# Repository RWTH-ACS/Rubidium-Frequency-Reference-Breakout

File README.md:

# Low-Cost Rubidium-Based Clock Reference

This project contains a hardware breakout board for an FE-5680A frequency reference, including a Python web UI to control the frequency offsets and monitor the PPS and Lock signal.

A detailed explanation is given in the publication proceedings of ISPCS 2026 (Low-Cost Rubidium-Based Clock Reference and Pulse-Per-Second Jitter Evaluation)

## Hardware

The hardware breakout board provides multiple decoupled 10 MHz outputs to allow for easy use in a laboratory environment. It also has a pulse per second output that is controllable in its pulse width.

## Software

The software stack allows for a simple control of the RFS via a Raspberry Pi. A USB to RS232 adapter that is connected to the RFS was utilized.

## License

This software is licensed under the Apache open-source license, while the hardware is under the CERN-OHL-W-2.0 open source license. Please refer to the license file in the `LICENSE` in the hardware and software directory.

We kindly ask all academic publications employing components of this work to cite the following paper:

For other licensing options please consult [Prof. Antonello Monti](mailto:amonti@eonerc.rwth-aachen.de).

## Contact

- Manuel Pitz <manuel.pitz@eonerc.rwth-aachen.de>
- Sebastian Uerlich <sebastian.uerlich@eonerc.rwth-aachen.de>
- Benish Khan <benish.khan@eonerc.rwth-aachen.de>
- Leonid Kalinin <leonid.kalinin@rwth-aachen.de>

[Institute for Automation of Complex Power Systems (ACS)](http://www.acs.eonerc.rwth-aachen.de)
[EON Energy Research Center (EONERC)](http://www.eonerc.rwth-aachen.de)
[RWTH University Aachen, Germany](http://www.rwth-aachen.de)

## Acknowledgment

This research has received funding from the European Union’s Horizon Europe research and innovation programme under grant agreement No 101172829. Views and opinions expressed are however those of the author(s) only and do not necessarily reflect those of the European Union or CINEA. Neither the European Union nor the granting authority can be held responsible for them.

We are grateful for the financial support of the [BMWE (Federal Ministry of Economic Affairs and Energy)](https://www.bundeswirtschaftsministerium.de/Navigation/EN/Home/home.html), funding reference [03EI6125A](https://www.enargus.de/pub/bscw.cgi/?op=enargus.eps2&q=beaver&v=10&id=243841191).

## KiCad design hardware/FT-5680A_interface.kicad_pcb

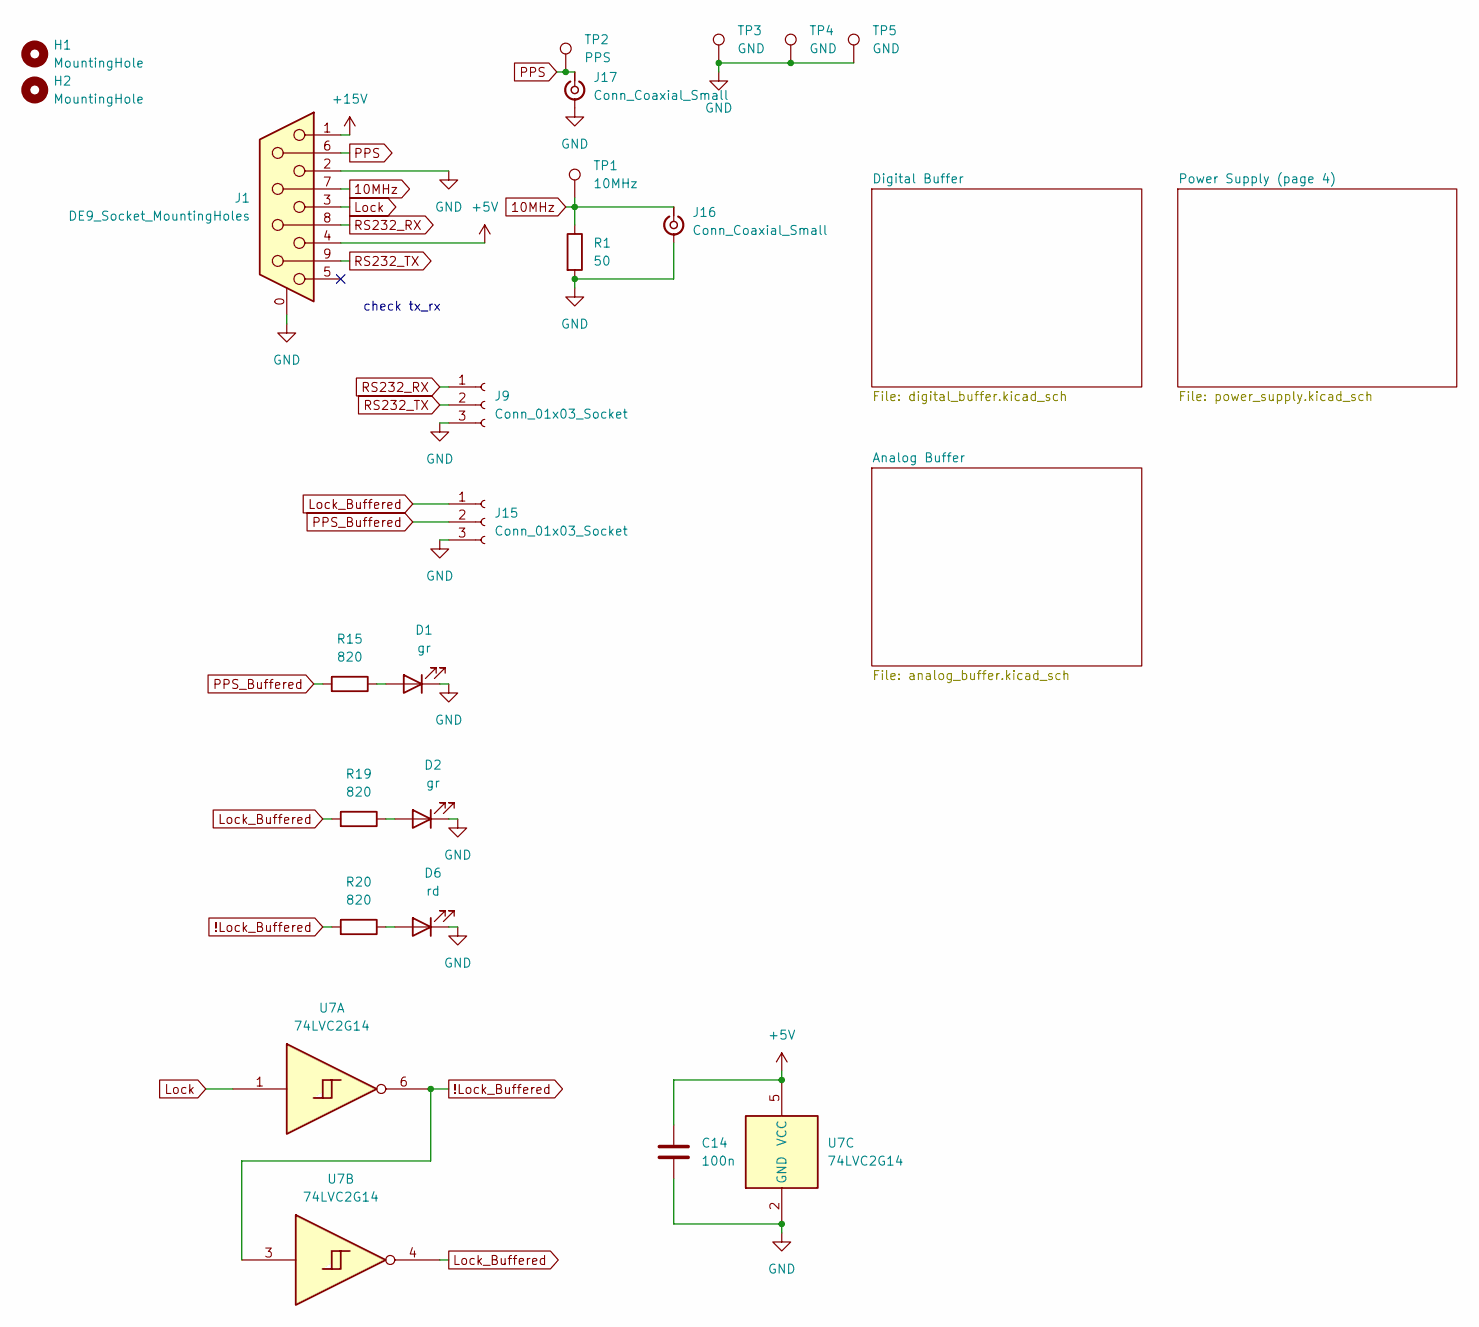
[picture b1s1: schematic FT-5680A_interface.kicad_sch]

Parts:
C14: 100n; C_0805_2012Metric_Pad1.18x1.45mm_HandSolder
D1, D2: gr; LED_0805_2012Metric_Pad1.15x1.40mm_HandSolder
D6: rd; LED_0805_2012Metric_Pad1.15x1.40mm_HandSolder
H1, H2: MountingHole; MountingHole_4.3mm_M4_DIN965
J1: DE9_Socket_MountingHoles; ASSMANN_A-DF_09_A_KG-T2S; Digikey AE10921-ND
J9, J15: Conn_01x03_Socket; 2601-3103; Digikey 2946-2601-3103-ND
J16, J17: Conn_Coaxial_Small; SMA_Molex_73251-1153_EdgeMount_Horizontal
R1: 50; R_0805_2012Metric_Pad1.20x1.40mm_HandSolder
R15, R19, R20: 820; R_0805_2012Metric_Pad1.20x1.40mm_HandSolder
TP1: 10MHz; PinHeader_1x01_P1.00mm_Vertical
TP2: PPS; PinHeader_1x01_P1.00mm_Vertical
TP3, TP4, TP5: GND; PinHeader_1x01_P1.00mm_Vertical
U7: 74LVC2G14; SOT-363_SC-70-6_Handsoldering; Digikey 296-13011-1-ND

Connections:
10MHz: J1.7, J16.1 (In), R1.1, TP1.1; also elsewhere on the board
!Lock_Buffered: R20.2, U7.3, U7.6
+5V: C14.1, J1.4, U7.5 (VCC); also elsewhere on the board
+15V: J1.1; also elsewhere on the board
GND: C14.2, D1.1 (K), D2.1 (K), D6.1 (K), J1.0 (PAD), J1.2, J9.3, J15.3, J16.2 (Ext), J17.2 (Ext), R1.2, TP3.1, TP4.1, TP5.1, U7.2 (GND); also elsewhere on the board
Lock: J1.3, U7.1
Lock_Buffered: J15.1, R19.2, U7.4
unnamed: D1.2 (A), R15.1
unnamed: D2.2 (A), R19.1
unnamed: D6.2 (A), R20.1
PPS: J1.6, J17.1 (In), TP2.1; also elsewhere on the board
PPS_Buffered: J15.2, R15.2; also elsewhere on the board
RS232_RX: J1.8, J9.1
RS232_TX: J1.9, J9.2

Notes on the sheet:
check tx_rx

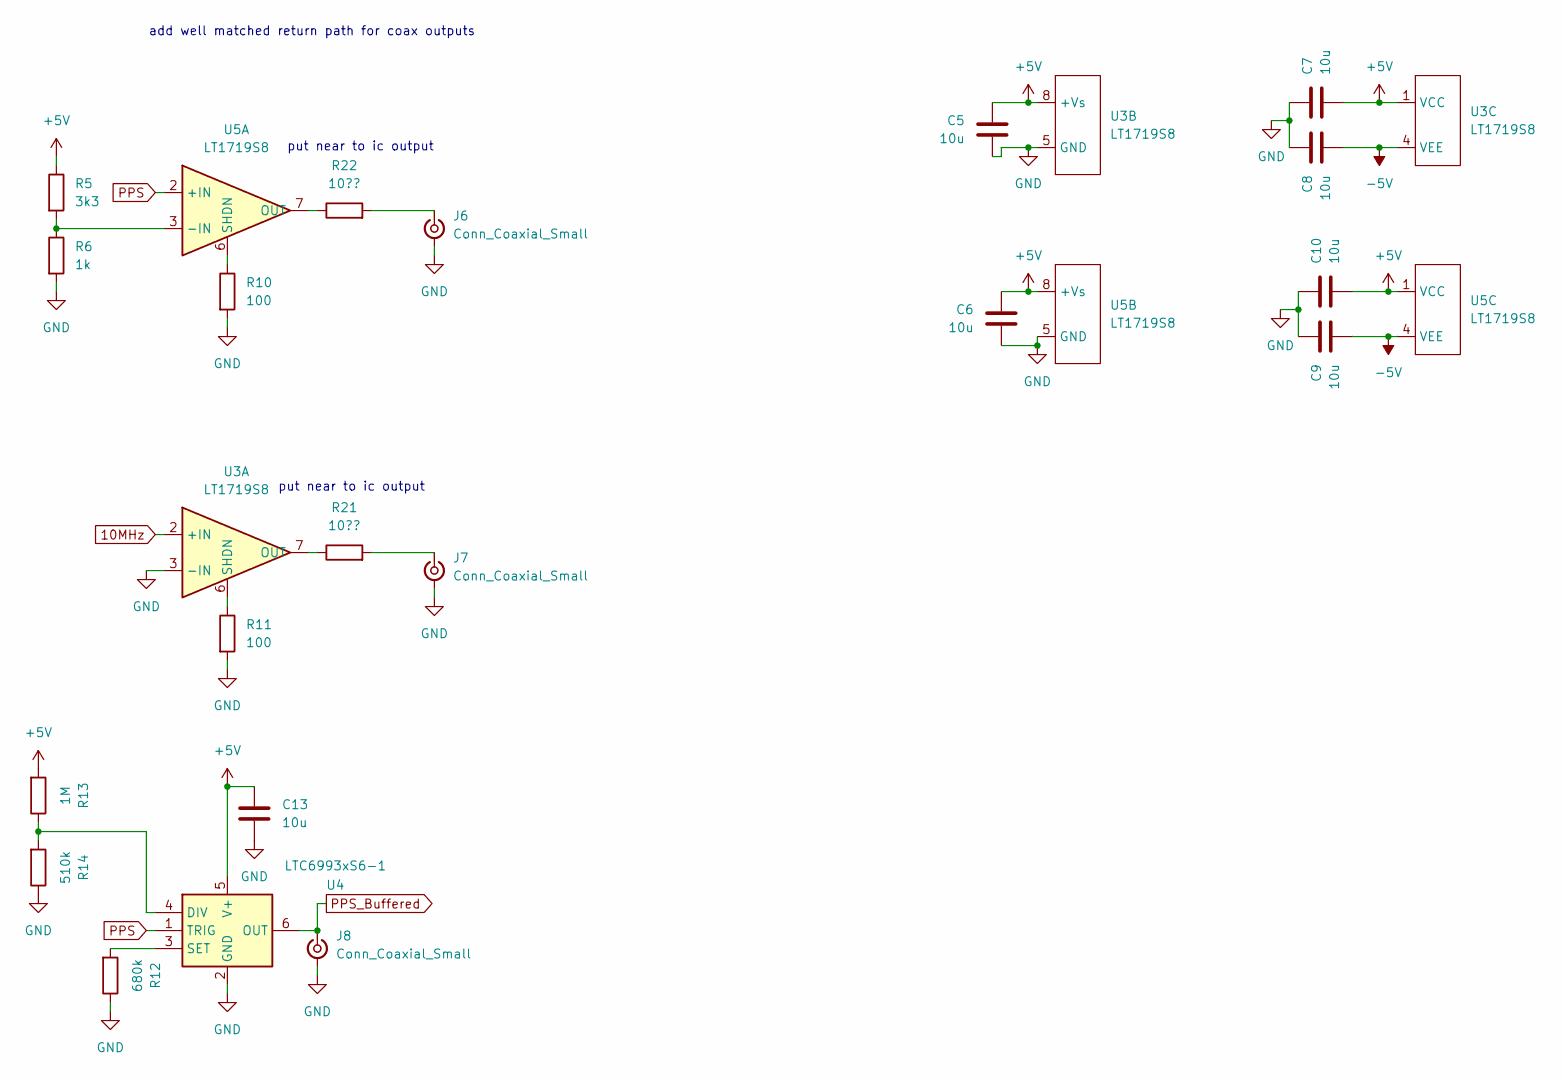
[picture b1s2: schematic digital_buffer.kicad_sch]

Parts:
C5, C6, C7, C8, C9, C10, C13: 10u; C_0805_2012Metric_Pad1.18x1.45mm_HandSolder
J6, J7, J8: Conn_Coaxial_Small; SMA_Molex_73251-1153_EdgeMount_Horizontal
R5: 3k3; R_0805_2012Metric_Pad1.20x1.40mm_HandSolder
R6: 1k; R_0805_2012Metric_Pad1.20x1.40mm_HandSolder
R10, R11: 100; R_0805_2012Metric_Pad1.20x1.40mm_HandSolder
R12: 680k; R_0805_2012Metric_Pad1.20x1.40mm_HandSolder
R13: 1M; R_0805_2012Metric_Pad1.20x1.40mm_HandSolder
R14: 510k; R_0805_2012Metric_Pad1.20x1.40mm_HandSolder
R21, R22: 10??; R_0805_2012Metric_Pad1.20x1.40mm_HandSolder
U3, U5: LT1719S8; SOIC-8_3.9x4.9mm_P1.27mm; Digikey 505-LT1719IS8#PBF-ND
U4: LTC6993xS6-1; TSOT-23-6_HandSoldering; Digikey 505-LTC6993HS6-1#WTRMPBFCT-ND

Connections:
10MHz: U3.2 (+IN); also elsewhere on the board
+5V: C5.1, C6.1, C7.2, C10.2, C13.1, R5.1, R13.2, U3.1 (VCC), U3.8 (+Vs), U4.5 (V+), U5.1 (VCC), U5.8 (+Vs); also elsewhere on the board
-5V: C8.2, C9.2, U3.4 (VEE), U5.4 (VEE); also elsewhere on the board
GND: C5.2, C6.2, C7.1, C8.1, C9.1, C10.1, C13.2, J6.2 (Ext), J7.2 (Ext), J8.2 (Ext), R6.2, R10.2, R11.2, R12.1, R14.1, U3.3 (-IN), U3.5 (GND), U4.2 (GND), U5.5 (GND); also elsewhere on the board
unnamed: J6.1 (In), R22.1, R22.2, U5.7 (OUT)
unnamed: J7.1 (In), R21.1, R21.2, U3.7 (OUT)
unnamed: R11.1, U3.6 (SHDN)
unnamed: R13.1, R14.2, U4.4 (DIV)
unnamed: R12.2, U4.3 (SET)
unnamed: R5.2, R6.1, U5.3 (-IN)
unnamed: R10.1, U5.6 (SHDN)
PPS: U4.1 (TRIG), U5.2 (+IN); also elsewhere on the board
PPS_Buffered: J8.1 (In), U4.6 (OUT); also elsewhere on the board

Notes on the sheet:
put near to ic output
add well matched return path for coax outputs

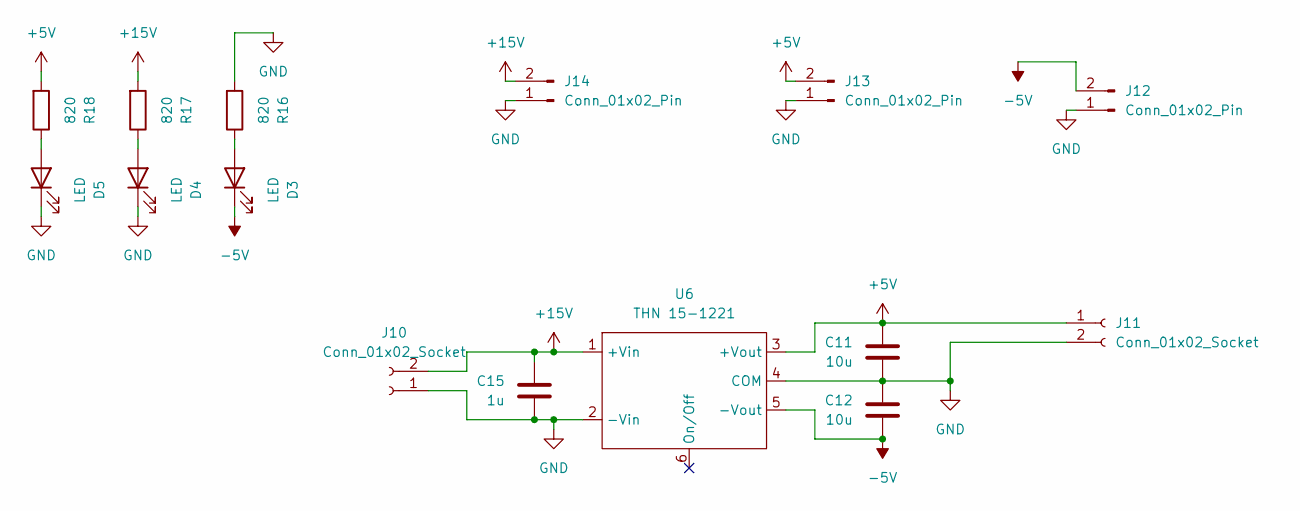
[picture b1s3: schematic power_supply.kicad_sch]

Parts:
C11, C12: 10u; C_0805_2012Metric_Pad1.18x1.45mm_HandSolder
C15: 1u; C_0805_2012Metric_Pad1.18x1.45mm_HandSolder
D3, D4, D5: LED; LED_0805_2012Metric_Pad1.15x1.40mm_HandSolder
J10, J11: Conn_01x02_Socket; 2601-3102; Digikey 2946-2601-3102-ND
J12, J13, J14: Conn_01x02_Pin; PinHeader_1x02_P2.54mm_Vertical
R16, R17, R18: 820; R_0805_2012Metric_Pad1.20x1.40mm_HandSolder
U6: THN 15-1221; Digikey 1951-3115-ND

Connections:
+5V: C11.1, J11.1, J13.2, R18.2, U6.3 (+Vout); also elsewhere on the board
+15V: C15.1, J10.2, J14.2, R17.2, U6.1 (+Vin); also elsewhere on the board
-5V: C12.2, D3.1 (K), J12.2, U6.5 (-Vout); also elsewhere on the board
GND: C11.2, C12.1, C15.2, D4.1 (K), D5.1 (K), J10.1, J11.2, J12.1, J13.1, J14.1, R16.2, U6.2 (-Vin), U6.4 (COM); also elsewhere on the board
unnamed: D3.2 (A), R16.1
unnamed: D4.2 (A), R17.1
unnamed: D5.2 (A), R18.1

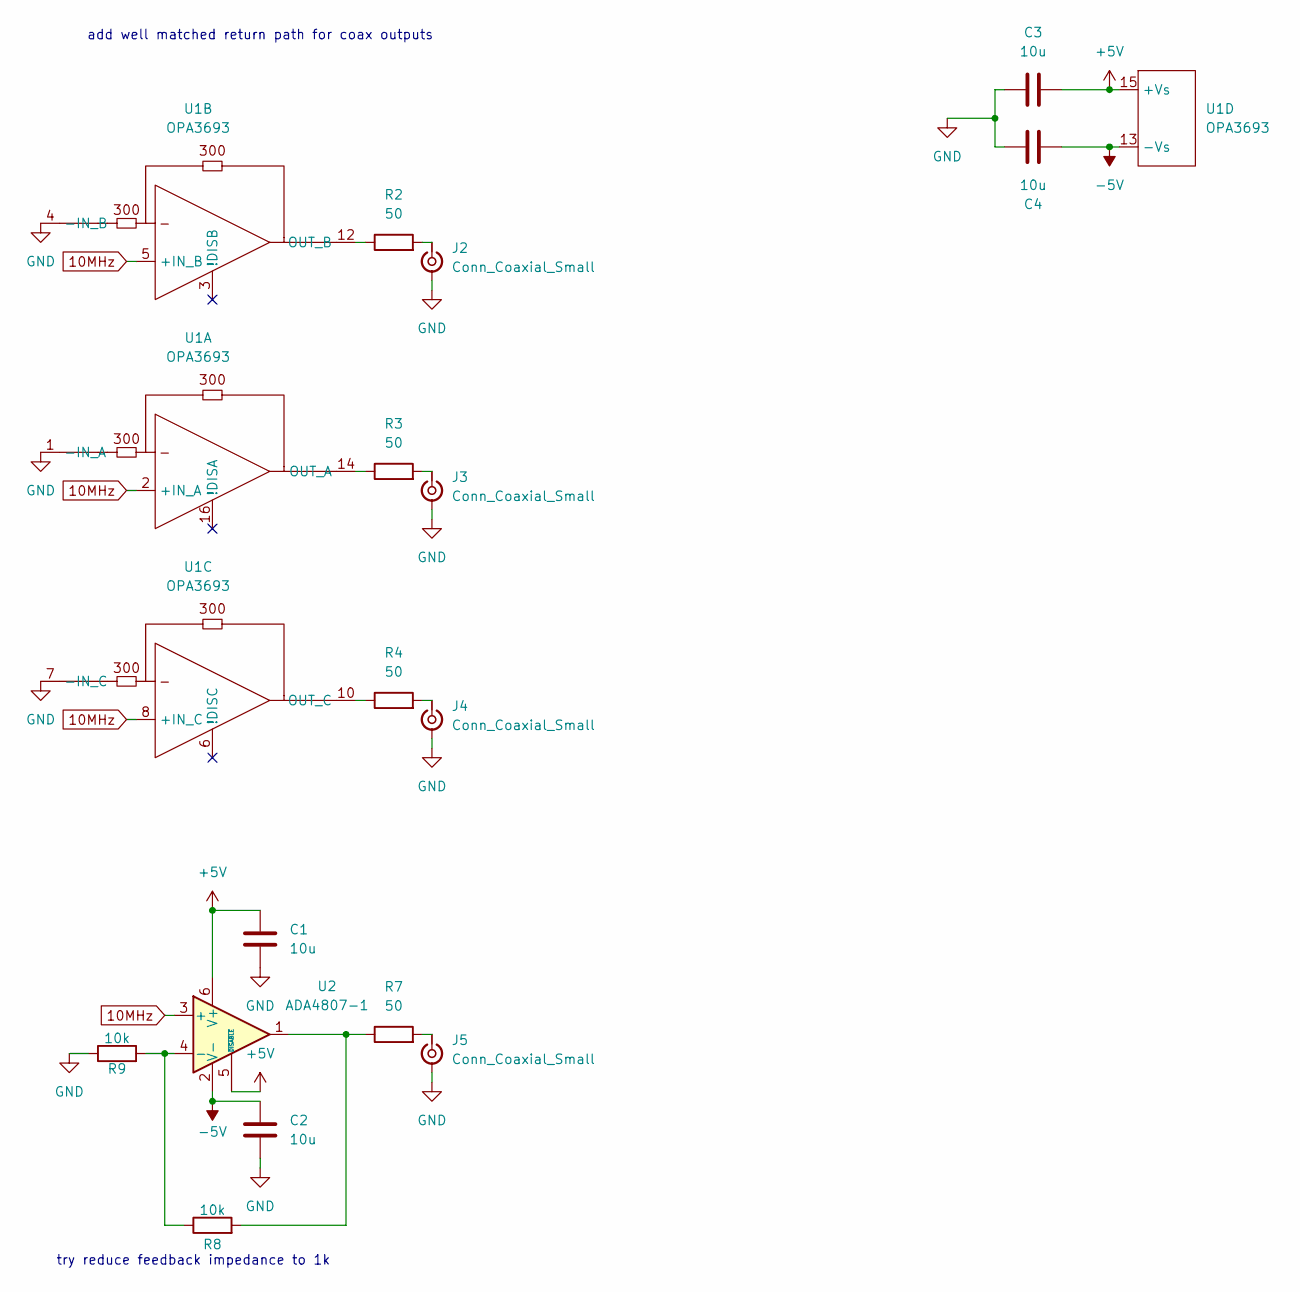
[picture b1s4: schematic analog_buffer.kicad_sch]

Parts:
C1, C2, C3, C4: 10u; C_0805_2012Metric_Pad1.18x1.45mm_HandSolder
J2, J3, J4, J5: Conn_Coaxial_Small; SMA_Molex_73251-1153_EdgeMount_Horizontal
R2, R3, R4, R7: 50; R_0805_2012Metric_Pad1.20x1.40mm_HandSolder
R8, R9: 10k; R_0805_2012Metric_Pad1.20x1.40mm_HandSolder
U1: OPA3693; SSOP-16_3.9x4.9mm_P0.635mm; Digikey 296-21393-5-ND
U2: ADA4807-1; SOT-23-6_Handsoldering; Digikey 505-ADA4807-1ARJZ-R7CT-ND

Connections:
10MHz: U1.2 (+IN_A), U1.5 (+IN_B), U1.8 (+IN_C), U2.3 (+); also elsewhere on the board
+5V: C1.1, C3.2, U1.11 (+Vs), U1.15 (+Vs), U2.5 (~DISABLE), U2.6 (V+); also elsewhere on the board
-5V: C2.1, C4.2, U1.9 (-Vs), U1.13 (-Vs), U2.2 (V-); also elsewhere on the board
GND: C1.2, C2.2, C3.1, C4.1, J2.2 (Ext), J3.2 (Ext), J4.2 (Ext), J5.2 (Ext), R9.1, U1.1 (-IN_A), U1.4 (-IN_B), U1.7 (-IN_C); also elsewhere on the board
unnamed: J2.1 (In), R2.2
unnamed: J3.1 (In), R3.2
unnamed: J4.1 (In), R4.2
unnamed: J5.1 (In), R7.2
unnamed: R7.1, R8.2, U2.1
unnamed: R3.1, U1.14 (OUT_A)
unnamed: R2.1, U1.12 (OUT_B)
unnamed: R4.1, U1.10 (OUT_C)
unnamed: R8.1, R9.2, U2.4 (-)

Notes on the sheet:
try reduce feedback impedance to 1k
add well matched return path for coax outputs

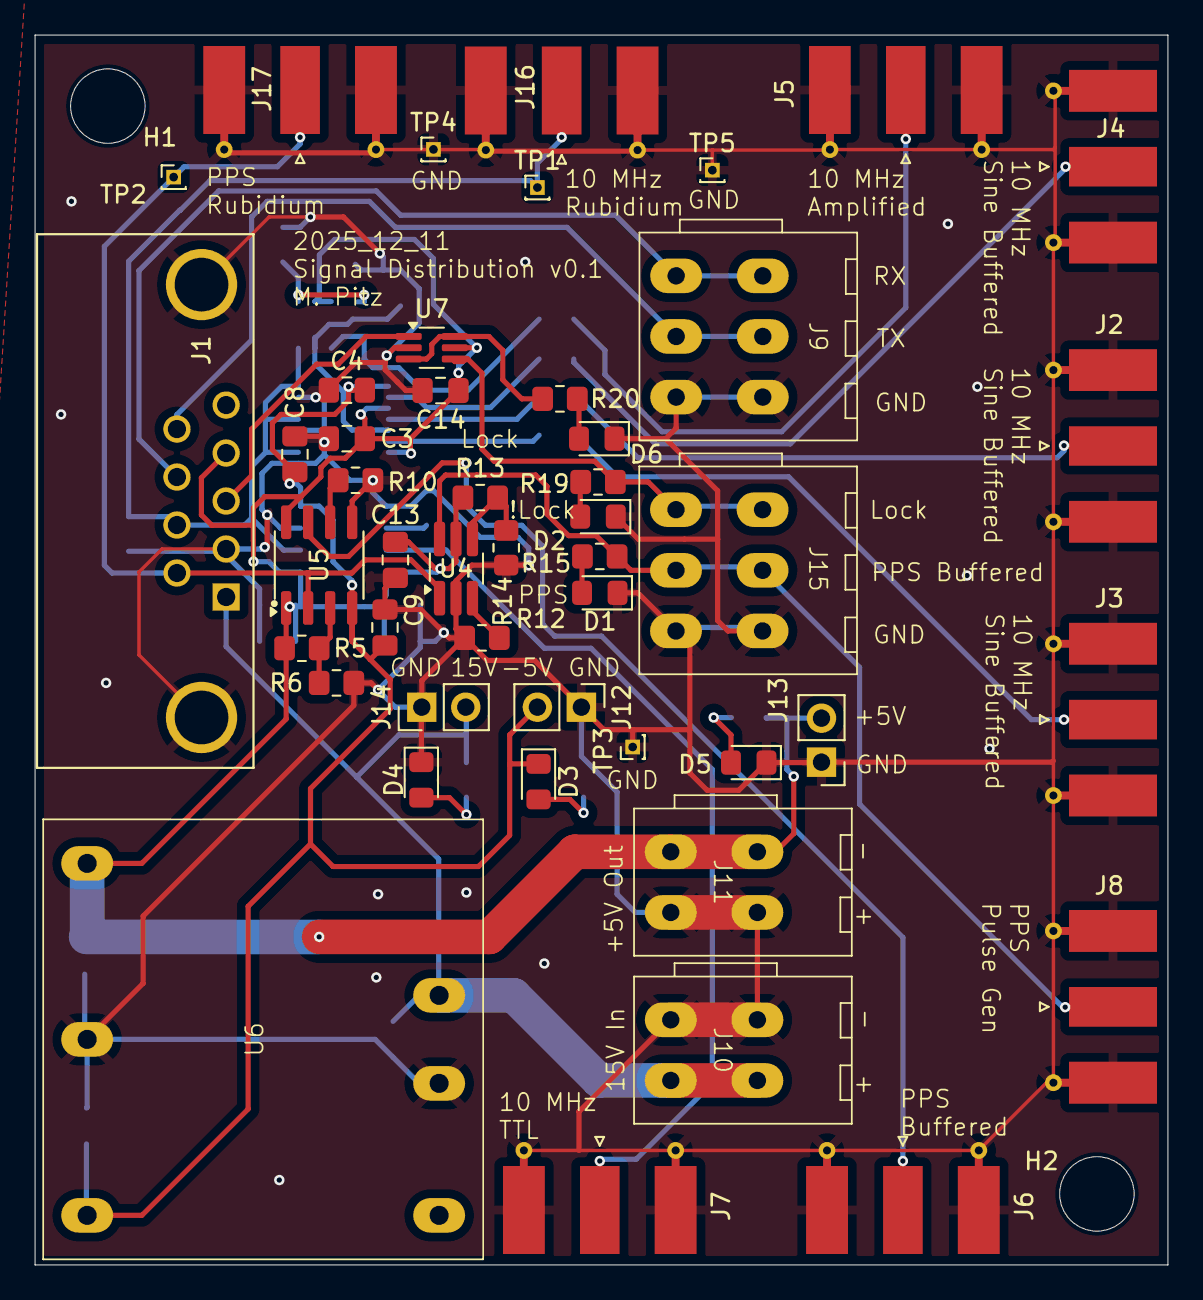
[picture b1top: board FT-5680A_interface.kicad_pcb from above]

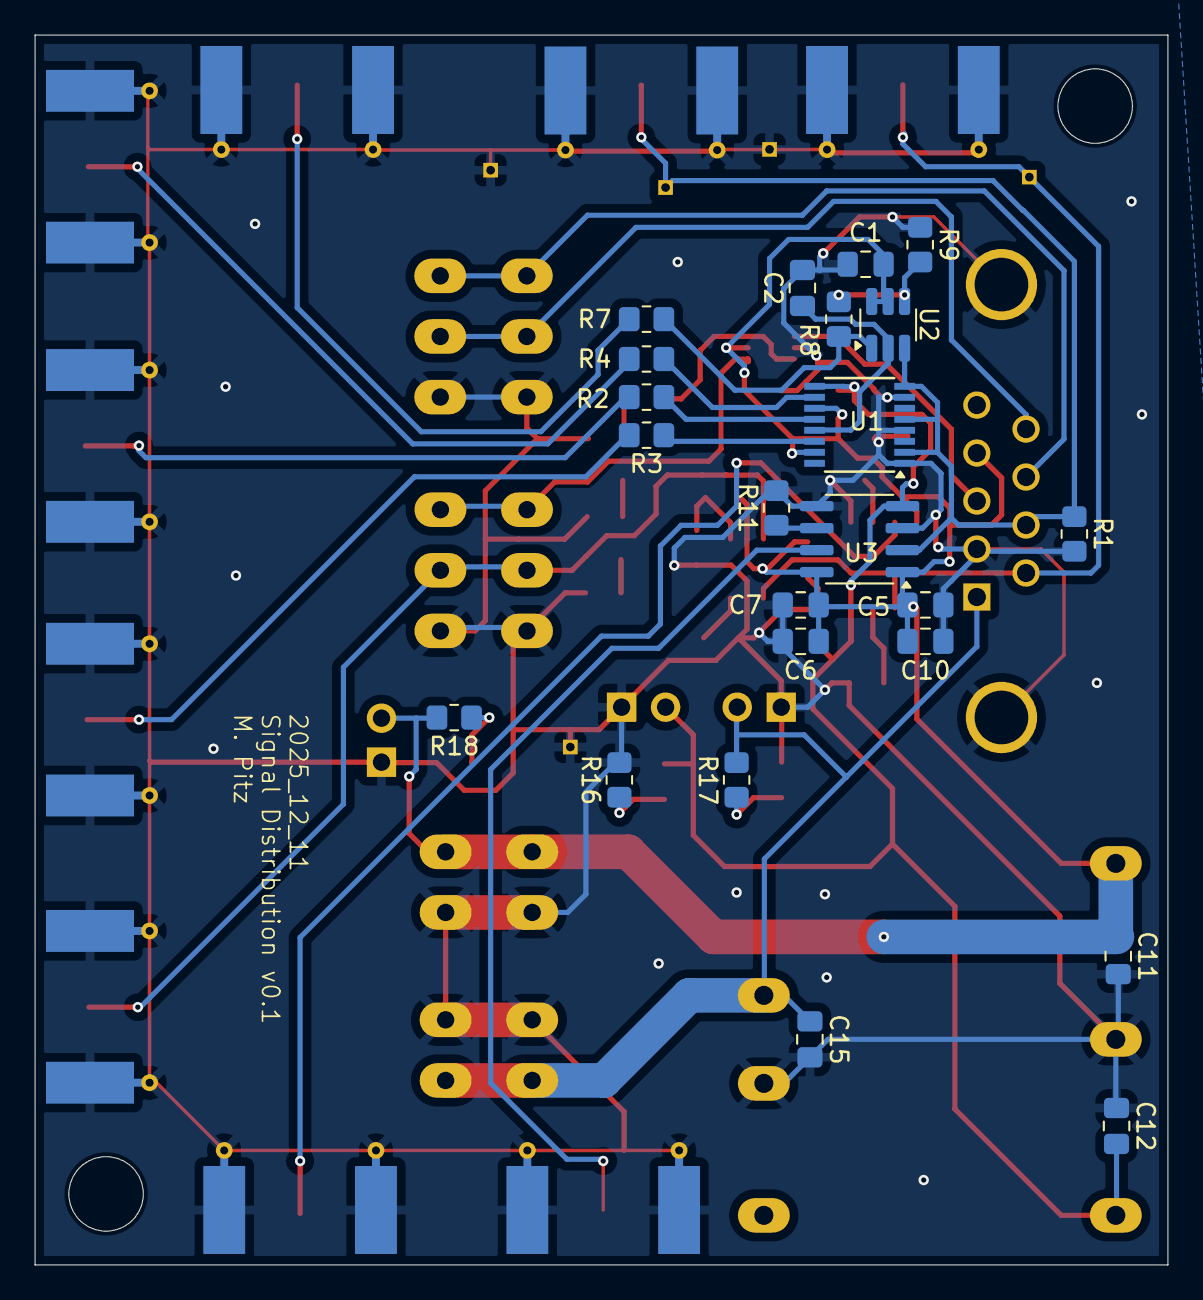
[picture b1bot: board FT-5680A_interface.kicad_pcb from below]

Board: 2 copper layers, 65.4 x 71.0 mm, 72 parts (23 on the bottom side), 34 nets.
